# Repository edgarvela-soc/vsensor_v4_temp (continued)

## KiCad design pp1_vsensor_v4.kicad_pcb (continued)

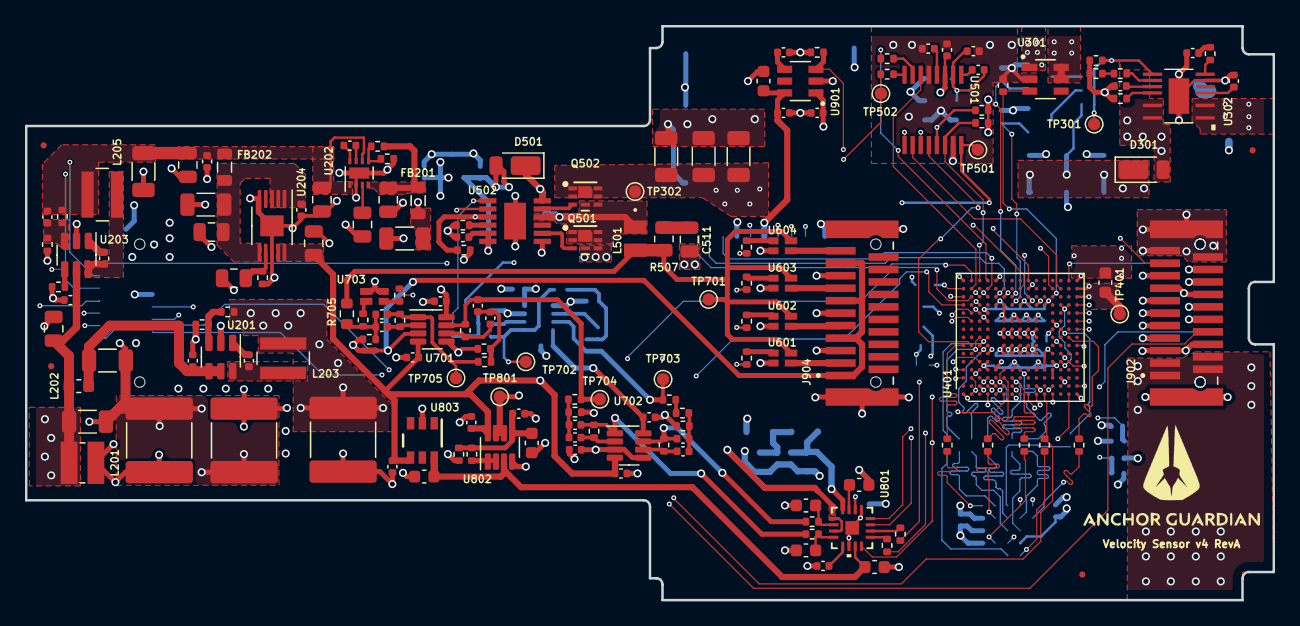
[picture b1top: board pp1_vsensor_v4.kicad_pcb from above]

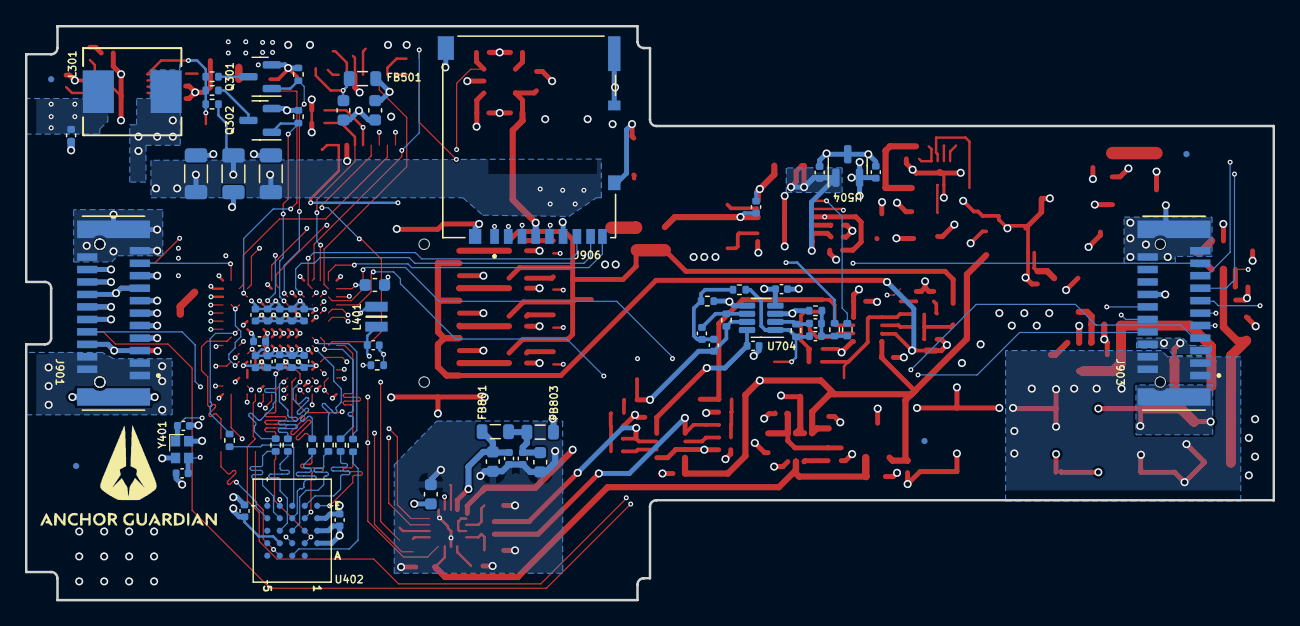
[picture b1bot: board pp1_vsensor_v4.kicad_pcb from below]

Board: 6 copper layers, 100.0 x 46.0 mm, 249 parts (77 on the bottom side), 175 nets.

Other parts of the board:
C302, C508, C509, C510: 1.5u; C_1206_3216Metric
C304, C305, C420: 1u; C_0402_1005Metric
C306: 2.2n; C_0402_1005Metric
Q301, Q302: PMV45EN2; SOT-23
R301: 1M; R_0402_1005Metric
R302: 34k8; R_0402_1005Metric
R303: 71k5; R_0402_1005Metric
R304: 130k; R_0402_1005Metric
R305: 22k1; R_0402_1005Metric
R306: 0R; R_0402_1005Metric
R309, R310, R311, R501, R502: 68k1; R_0402_1005Metric
TP301: VFBDRIVE; TestPoint_Pad_D1.0mm
U302: LT8361; SOP50P490X110-17N

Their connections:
+3V3: C420.1, R501.1, R502.1; also elsewhere on the board
/High Voltage Supply/SWBOOST: U302.14 (SW2), U302.16 (SW1); also elsewhere on the board
/High Voltage Supply/Sync_Mode: R306.1, U302.12 (SYNC/MODE)
/High Voltage Supply/VDriveIN: C305.1, U302.1 (EN/UVLO), U302.3 (VIN); also elsewhere on the board
/High Voltage Supply/VSel0: Q301.1 (G), R310.1; also elsewhere on the board
/High Voltage Supply/VSel1: Q302.1 (G), R309.1; also elsewhere on the board
/Microcontroller/DDS_FSync: R502.2; also elsewhere on the board
/Microcontroller/DDS_Standby: R501.2; also elsewhere on the board
/Microcontroller/HV_ENABLE: R311.1; also elsewhere on the board
unnamed: Q301.3 (D), R302.2
unnamed: Q302.3 (D), R303.2
unnamed: R301.2, R302.1, R303.1, R304.1, TP301.1, U302.9 (FBX)
unnamed: C304.1, U302.5 (INTVCC)
unnamed 132: U302.10 (RT); also elsewhere on the board
unnamed 133: U302.11 (SS); also elsewhere on the board
unnamed: R305.1, U302.8 (VC)

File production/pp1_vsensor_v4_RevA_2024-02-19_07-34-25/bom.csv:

Designator,Footprint,Quantity,Value,LCSC Part #
"C201, C206, C213, C214, C215, C218, C403, C404, C405, C406, C407, C408, C409, C410, C411, C412, C419, C501, C504, C506, C513, C515, C707, C714, C715, C716, C717, C718, C719, C801, C805, C812, C813, C814, C904",0402,35,100n,CC0402KRX7R9BB104
"C202, C203, C207",2220,3,22u,C5750X7R1H226M250KB
"C204, C205",1206,2,4u7,GRM31CR71H475KA12K
"C208, C209, C211, C220, C223, C225, C226",0805,7,4u7,CGA4J3X5R1H475K125AB
"C210, C304, C305, C420, C507, C512, C809, C901, C902",0402,9,1u,UMK105CBJ105MV-F
"C212, C219, C222",1206,3,47u,C3216X5R1C476M160AB
C216,0402,1,39p,CC0402FRNPO9BN390
C217,0805,1,2u2,CGA4J1X7R1V225K125AC
"C301, C302, C303, C508, C509, C510",1206,6,1.5u,C3216X7S2A155K160AB
C306,0402,1,2.2n,C0402C222J5RAC7867
"C307, C502",0402,2,10n,GCM155R71H103KA55D
"C401, C402",0402,2,9p,GRM1555C1H9R0BA01D
C413,0402,1,4u7,04023D475MAT2A
C415,0402,1,220p,0402N221J500CT
"C416, C421, C503, C505, C802, C810, C811, C815, C903",0603,9,10u,GRM188R61E106MA73D
"C701, C704, C708, C711",0402,4,15p,CC0402JRNPO9BN150
"C702, C705, C709, C712",0402,4,20p,CC0402JRNPO9BN200
"C703, C706, C710, C713",0402,4,24p,CC0402JRNPO9BN240
"C803, C804, C806",0603,3,1u,06035C105KAT2A
"C807, C808",0603,2,2n7,CC0603KRX7R9BB272
"D301, D501",D_PowerDI-123,2,DFLS2100-7,DFLS2100-7
"FB201, FB202, FB501, FB801, FB803",0805,5,2.2k/200mA,742792093
"J901, J903",AMPHENOL_10162581-3134121LF,2,10162581-3134121LF,10162581-3134121LF
"J902, J904",AMPHENOL_10162582-1134121LF,2,10162582-1134121LF,10162582-1134121LF
L201,L_Wuerth_MAPI-3020,1,10u,74438336100
L202,0603,1,470nH,LQM18PNR47NC0L
"L203, L205",L_Wuerth_MAPI-4020,2,15u 1.9A,74438356150
L301,IND25X25CZ,1,8u2,IHLP2525CZER8R2M01
L401,Inductor_0806,1,2.2u,DFE201612PD-2R2M=P2
L501,RES_CIGT201610,1,1u/4.2A,CIGT201610EH1R0MNE
"Q301, Q302",SOT-23,2,PMV45EN2,PMV45EN2R
"Q501, Q502",UDFN6B_TOS,2,SSM6K361NU,"SSM6K361NU,LF"
R201,0402,1,69k8,RC0402FR-0769K8L
R202,0402,1,91k,RC0402FR-0791KL
"R203, R209, R305",0402,3,22k1,RC0402FR-0722K1L
"R204, R210, R702, R713",0402,4,40k2,RC0402FR-0740K2L
R207,0402,1,102k,RC0402FR-07102KL
"R208, R309, R310, R311, R501, R502, R505, R703, R712, R720, R912",0402,11,68k1,RC0402FR-0768K1L
R301,0402,1,1M,CRGCQ0402F1M0
R302,0402,1,34k8,RMCF0402FT34K8
"R303, R701",0402,2,71k5,RC0402FR-0771K5L
R304,0402,1,130k,RC0402FR-07130KL
R306,0402,1,0R,RC0402JR-070RL
"R307, R308, R401, R714, R715, R721, R722, R806, R807",0402,9,10k,RC1005F103CS
"R402, R403, R404, R405, R406, R407, R408, R409, R410, R411, R412, R413, R503, R504",0402,14,33R,RC0402JR-0733RL
R506,0402,1,36k5,ERJ-2RKF3652X
"R601, R602, R603, R604, R710",0402,5,270R,RMCF0402FT270R
R704,0402,1,20k5,RC0402FR-0720K5L
R705,0603,1,100k,RC0402FR-07100KL
R706,0402,1,19k6,RC0402FR-0719K6L
"R707, R709, R717, R718",0402,4,2k55,RC0402FR-072K55L
R708,0402,1,1k58,RC0402FR-071K58L
"R711, R719",0402,2,1k47,RC0402FR-071K47L
"R801, R802",0402,2,20R,RC0402FR-0720RL
"R803, R804",0402,2,100R,RC0402FR-07100RL
"U201, U203",SOT-23-6,2,LMR54406,LMR54406FDBVR
U202,WSON-8-1EP_2x2mm_P0.5mm_EP0.9x1.6mm,1,LM27761,LM27761DSGR
U204,MSOP-10-1EP_3x3mm_P0.5mm_EP1.68x1.88mm,1,LT3042EMSE,LT3042EMSE#TRPBF
"U301, U901",SOT95P280X145-6N,2,TPS22810DBV,TPS22810TDBVRQ1
U302,SOP50P490X110-17N,1,LT8361,LT8361HMSE#PBF
U401,UFBGA-201_10x10mm_Layout15x15_P0.65mm,1,STM32H725IGK6,STM32H725IGK6
U402,S27KS0642GABHV020_1,1,S70KL1282,S70KL1282GABHV020
U501,AD5932YRUZ,1,AD5932YRUZ,AD5932YRUZ
U502,LTC7060,1,LTC7060IMSE-PBF,LTC7060IMSE#WTRPBF
U504,SOT-23,1,TLV760_12,TLV76012DBZR
"U601, U602, U603, U604, U703",TLP3409STP_E,5,TLP3409STP_E,"TLP3409S(TP,E"
"U701, U702, U704, U802",SOT-23-8,4,AD8039,AD8039ARTZ-REEL7
U801,AD7383,1,AD7383,AD7383BCPZ-RL7
U803,REF3430,1,REF3430,REF3430TIDBVR
Y401,XTAL_ECS-160-9-37-CKM-TR,1,ECX-1637_25MHz,ECS-250-8-37-RWN-TR

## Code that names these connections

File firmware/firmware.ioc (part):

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Mcu.Name=STM32H725IGKx
Mcu.Package=UFBGA176
Mcu.UserName=STM32H725IGKx
PA0.GPIOParameters=GPIO_Label
PA0.GPIO_Label=TIM_CS
PA0.Signal=S_TIM2_CH1_ETR
PA0_C.GPIOParameters=GPIO_Label
PA0_C.GPIO_Label=AIN_1
PA0_C.Signal=ADCx_INP0
PA11.GPIOParameters=GPIO_Label
PA11.GPIO_Label=DDS_STANDBY
PA11.Signal=GPIO_Output
PA13(JTMS/SWDIO).Mode=Serial_Wire
PA13(JTMS/SWDIO).Signal=DEBUG_JTMS-SWDIO
PA14(JTCK/SWCLK).Mode=Serial_Wire
PA14(JTCK/SWCLK).Signal=DEBUG_JTCK-SWCLK
PA1_C.GPIOParameters=GPIO_Label
PA1_C.GPIO_Label=AIN_2
PA1_C.Signal=ADCx_INP1
PA3.GPIOParameters=GPIO_Label
PA3.GPIO_Label=TIM_SCLK
PA3.Signal=S_TIM15_CH2
PA4.GPIOParameters=GPIO_Label
PA4.GPIO_Label=DDS_FSYNC
PA4.Mode=NSS_Signal_Hard_Output
PA4.Signal=SPI6_NSS
PA6.GPIOParameters=GPIO_Label
PA6.GPIO_Label=DDS_INTERRUPT
PA6.Signal=S_TIM13_CH1
PA7.GPIOParameters=GPIO_Label
PA7.GPIO_Label=DDS_SDA
PA7.Mode=Simplex_Bidirectional_Master
PA7.Signal=SPI6_MOSI
PA8.Mode=Clock-out-1
PA8.Signal=RCC_MCO_1
PA9.GPIOParameters=GPIO_Label
PA9.GPIO_Label=DRV_FAULT
PA9.Signal=GPIO_Input
PB10.GPIOParameters=GPIO_Label
PB10.GPIO_Label=ADC_SCLKA
PB10.Mode=Full_Duplex_Slave
PB10.Signal=SPI2_SCK
PB9.GPIOParameters=GPIO_Label
PB9.GPIO_Label=ADC_CSA
PB9.Mode=NSS_Signal_Hard_Input
PB9.Signal=SPI2_NSS
PC10.GPIOParameters=GPIO_Label
PC10.GPIO_Label=SD_D2
PC10.Mode=SD_4_bits_Wide_bus
PC10.Signal=SDMMC1_D2
PC11.GPIOParameters=GPIO_Label
PC11.GPIO_Label=SD_D3
PC11.Mode=SD_4_bits_Wide_bus
PC11.Signal=SDMMC1_D3
PC12.GPIOParameters=GPIO_Label
PC12.GPIO_Label=SD_CLK
PC12.Mode=SD_4_bits_Wide_bus
PC12.Signal=SDMMC1_CK
PC14-OSC32_IN.GPIOParameters=GPIO_Label
PC14-OSC32_IN.GPIO_Label=Rx_Ena
PC14-OSC32_IN.Signal=GPIO_Output
PC2.GPIOParameters=GPIO_Label
PC2.GPIO_Label=ADC_SDI
PC2.Mode=Full_Duplex_Slave
PC2.Signal=SPI2_MISO
PC3.GPIOParameters=GPIO_Label
PC3.GPIO_Label=ADC_SDOA
PC3.Mode=Full_Duplex_Slave
PC3.Signal=SPI2_MOSI
PC7.GPIOParameters=GPIO_Label
PC7.GPIO_Label=DDS_SYNCOUT
PC7.Signal=GPIO_Input
PC8.GPIOParameters=GPIO_Label
PC8.GPIO_Label=SD_D0
PC8.Mode=SD_4_bits_Wide_bus
PC8.Signal=SDMMC1_D0
PC9.GPIOParameters=GPIO_Label
PC9.GPIO_Label=SD_D1
PC9.Mode=SD_4_bits_Wide_bus
PC9.Signal=SDMMC1_D1
PD12.GPIOParameters=GPIO_Label
PD12.GPIO_Label=VSEN_D1
PD12.Signal=GPIO_Output
PD14.GPIOParameters=GPIO_Label
PD14.GPIO_Label=VSENS_uc_RX
PD14.Mode=Asynchronous
PD14.Signal=UART9_RX
PD15.GPIOParameters=GPIO_Label
PD15.GPIO_Label=VSENS_uc_TX
PD15.Mode=Asynchronous
PD15.Signal=UART9_TX
PD2.GPIOParameters=GPIO_Label
PD2.GPIO_Label=SD_CMD
PD2.Mode=SD_4_bits_Wide_bus
PD2.Signal=SDMMC1_CMD
PE1.GPIOParameters=GPIO_Label
PE1.GPIO_Label=VSENS_D2
PE1.Signal=GPIO_Output
PE12.GPIOParameters=GPIO_Label
PE12.GPIO_Label=ADC_SCLKB
PE12.Mode=Simplex_Bidirectional_Slave
PE12.Signal=SPI4_SCK
PE4.GPIOParameters=GPIO_Label
PE4.GPIO_Label=ADC_CSB
PE4.Mode=NSS_Signal_Hard_Input
PE4.Signal=SPI4_NSS
PE5.GPIOParameters=GPIO_Label
PE5.GPIO_Label=ADC_SDOB
PE5.Mode=Simplex_Bidirectional_Slave
PE5.Signal=SPI4_MISO
PF0.GPIOParameters=GPIO_Label
PF0.GPIO_Label=uc_dram_dq0
PF0.Mode=OCTOSPI2_IOL_Port2L
PF0.Signal=OCTOSPIM_P2_IO0
PF1.GPIOParameters=GPIO_Label
PF1.GPIO_Label=uc_dram_dq1
PF1.Mode=OCTOSPI2_IOL_Port2L
PF1.Signal=OCTOSPIM_P2_IO1
PF11.GPIOParameters=GPIO_Label
PF11.GPIO_Label=DRV_EN
PF11.Mode=PWM Generation1 CH1
PF11.Signal=TIM24_CH1
PF2.GPIOParameters=GPIO_Label
PF2.GPIO_Label=uc_dram_dq2
PF2.Mode=OCTOSPI2_IOL_Port2L
PF2.Signal=OCTOSPIM_P2_IO2
PF3.GPIOParameters=GPIO_Label
PF3.GPIO_Label=uc_dram_dq3
PF3.Mode=OCTOSPI2_IOL_Port2L
PF3.Signal=OCTOSPIM_P2_IO3
PF4.GPIOParameters=GPIO_Label
PF4.GPIO_Label=uc_dram_ck
PF4.Mode=O2_P2_CLK
PF4.Signal=OCTOSPIM_P2_CLK
PG0.GPIOParameters=GPIO_Label
PG0.GPIO_Label=uc_dram_dq4
PG0.Mode=OCTOSPI2_IOH_Port2H
PG0.Signal=OCTOSPIM_P2_IO4
PG1.GPIOParameters=GPIO_Label
PG1.GPIO_Label=uc_dram_dq5
PG1.Mode=OCTOSPI2_IOH_Port2H
PG1.Signal=OCTOSPIM_P2_IO5
PG10.GPIOParameters=GPIO_Label
PG10.GPIO_Label=uc_dram_dq6
PG10.Mode=OCTOSPI2_IOH_Port2H
PG10.Signal=OCTOSPIM_P2_IO6
PG11.GPIOParameters=GPIO_Label
PG11.GPIO_Label=uc_dram_dq7
PG11.Mode=OCTOSPI2_IOH_Port2H
PG11.Signal=OCTOSPIM_P2_IO7
PG12.GPIOParameters=GPIO_Label
PG12.GPIO_Label=uc_dram_ncs
PG12.Mode=OCTOSPI2_Port2_NCS
PG12.Signal=OCTOSPIM_P2_NCS
PG13.GPIOParameters=GPIO_Label
PG13.GPIO_Label=DDS_SCLK
PG13.Mode=Simplex_Bidirectional_Master
PG13.Signal=SPI6_SCK
PG15.GPIOParameters=GPIO_Label
PG15.GPIO_Label=uc_dram_rwds
PG15.Mode=OCTOSPI2_Port2_DQS
PG15.Signal=OCTOSPIM_P2_DQS
PH10.GPIOParameters=GPIO_Label
PH10.GPIO_Label=DDS_CTRL
PH10.Signal=S_TIM5_CH1
PH14.GPIOParameters=GPIO_Label
PH14.GPIO_Label=SD_EN3V3
PH14.Signal=GPIO_Output
PH15.GPIOParameters=GPIO_Label
PH15.GPIO_Label=SD_DETECT
PH15.Signal=GPIO_Output
PH9.GPIOParameters=GPIO_Label
PH9.GPIO_Label=VSENS_D0
PH9.Signal=S_TIM12_CH2
RCC.SYSCLKFreq_VALUE=64000000
board=custom

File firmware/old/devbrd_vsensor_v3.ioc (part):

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Mcu.Name=STM32H735IGKx
Mcu.Package=UFBGA176
Mcu.UserName=STM32H735IGKx
PA0.Signal=S_TIM2_CH1_ETR
PA3.Signal=S_TIM15_CH2
PA5.GPIOParameters=GPIO_Label
PA5.GPIO_Label=DDS_SCLK
PA5.Mode=Simplex_Bidirectional_Master
PA5.Signal=SPI6_SCK
PA8.GPIOParameters=GPIO_Label
PA8.GPIO_Label=DDS_MCLK 
PA8.Mode=Clock-out-1
PA8.Signal=RCC_MCO_1
PB14.GPIOParameters=GPIO_Speed,GPIO_Label
PB14.GPIO_Label=ADC_SDI
PB14.GPIO_Speed=GPIO_SPEED_FREQ_VERY_HIGH
PB14.Mode=Full_Duplex_Slave
PB14.Signal=SPI2_MISO
PB15.GPIOParameters=GPIO_Speed,GPIO_Label
PB15.GPIO_Label=ADC_SDOA
PB15.GPIO_Speed=GPIO_SPEED_FREQ_VERY_HIGH
PB15.Mode=Full_Duplex_Slave
PB15.Signal=SPI2_MOSI
PB9.GPIOParameters=GPIO_Speed,GPIO_Label
PB9.GPIO_Label=ADC_CS
PB9.GPIO_Speed=GPIO_SPEED_FREQ_VERY_HIGH
PB9.Mode=NSS_Signal_Hard_Input
PB9.Signal=SPI2_NSS
PC10.GPIOParameters=GPIO_PuPd
PC10.GPIO_PuPd=GPIO_PULLUP
PC10.Mode=SD_4_bits_Wide_bus
PC10.Signal=SDMMC1_D2
PC11.GPIOParameters=GPIO_PuPd
PC11.GPIO_PuPd=GPIO_PULLUP
PC11.Mode=SD_4_bits_Wide_bus
PC11.Signal=SDMMC1_D3
PC12.Mode=SD_4_bits_Wide_bus
PC12.Signal=SDMMC1_CK
PC13.GPIOParameters=GPIO_Label
PC13.GPIO_Label=USR_BTN
PC13.Signal=GPIO_Input
PC2.GPIOParameters=GPIO_Label
PC2.GPIO_Label=LED_GREEN
PC2.Signal=GPIO_Output
PC3.GPIOParameters=GPIO_Label
PC3.GPIO_Label=LED_RED
PC3.Signal=GPIO_Output
PC8.GPIOParameters=GPIO_PuPd
PC8.GPIO_PuPd=GPIO_PULLUP
PC8.Mode=SD_4_bits_Wide_bus
PC8.Signal=SDMMC1_D0
PC9.GPIOParameters=GPIO_PuPd
PC9.GPIO_PuPd=GPIO_PULLUP
PC9.Mode=SD_4_bits_Wide_bus
PC9.Signal=SDMMC1_D1
PD14.GPIOParameters=GPIO_Label
PD14.GPIO_Label=VSEL1
PD14.Signal=GPIO_Output
PD15.GPIOParameters=GPIO_Label
PD15.GPIO_Label=EN_5V0
PD15.Signal=GPIO_Output
PD2.GPIOParameters=GPIO_PuPd
PD2.GPIO_PuPd=GPIO_PULLUP
PD2.Mode=SD_4_bits_Wide_bus
PD2.Signal=SDMMC1_CMD
PD3.GPIOParameters=GPIO_Speed,GPIO_Label
PD3.GPIO_Label=ADC_SCLK
PD3.GPIO_Speed=GPIO_SPEED_FREQ_VERY_HIGH
PD3.Mode=Full_Duplex_Slave
PD3.Signal=SPI2_SCK
PE10.GPIOParameters=GPIO_Label
PE10.GPIO_Label=XDCR_SEL2
PE10.Signal=GPIO_Output
PE11.GPIOParameters=GPIO_Speed,GPIO_Label
PE11.GPIO_Label=ADC_CS2
PE11.GPIO_Speed=GPIO_SPEED_FREQ_VERY_HIGH
PE11.Mode=NSS_Signal_Hard_Input
PE11.Signal=SPI4_NSS
PE12.GPIOParameters=GPIO_Speed,GPIO_Label
PE12.GPIO_Label=ADC_SCLK2
PE12.GPIO_Speed=GPIO_SPEED_FREQ_VERY_HIGH
PE12.Mode=Simplex_Bidirectional_Slave
PE12.Signal=SPI4_SCK
PE13.GPIOParameters=GPIO_Speed,GPIO_Label
PE13.GPIO_Label=ADC_SDOB
PE13.GPIO_Speed=GPIO_SPEED_FREQ_VERY_HIGH
PE13.Mode=Simplex_Bidirectional_Slave
PE13.Signal=SPI4_MISO
PE14.GPIOParameters=GPIO_Label
PE14.GPIO_Label=DRV_FAULT
PE14.Signal=GPIO_Input
PE7.GPIOParameters=GPIO_Label
PE7.GPIO_Label=VSEL2
PE7.Signal=GPIO_Output
PE9.GPIOParameters=GPIO_Label
PE9.GPIO_Label=XDCR_SEL1
PE9.Signal=GPIO_Output
PF0.Mode=OCTOSPI2_IOL_Port2L
PF0.Signal=OCTOSPIM_P2_IO0
PF1.Mode=OCTOSPI2_IOL_Port2L
PF1.Signal=OCTOSPIM_P2_IO1
PF11.Signal=TIM24_CH1
PF12.Mode=OCTOSPI2_Port2_DQS
PF12.Signal=OCTOSPIM_P2_DQS
PF13.GPIOParameters=GPIO_Label
PF13.GPIO_Label=XDCR_SEL3
PF13.Signal=GPIO_Output
PF14.GPIOParameters=GPIO_PuPd,GPIO_Label
PF14.GPIO_Label=DDS_STANDBY
PF14.GPIO_PuPd=GPIO_PULLDOWN
PF14.Signal=GPIO_Output
PF15.GPIOParameters=GPIO_Label
PF15.GPIO_Label=SD_EN3V3
PF15.Signal=GPIO_Output
PF2.Mode=OCTOSPI2_IOL_Port2L
PF2.Signal=OCTOSPIM_P2_IO2
PF3.Mode=OCTOSPI2_IOL_Port2L
PF3.Signal=OCTOSPIM_P2_IO3
PF4.Mode=O2_P2_CLK
PF4.Signal=OCTOSPIM_P2_CLK
PF5.GPIOParameters=GPIO_Label
PF5.GPIO_Label=SD_DETECT
PF5.Signal=GPIO_Input
PF6.GPIOParameters=GPIO_Speed,PinState,GPIO_Label
PF6.GPIO_Label=DDS_FSYNC
PF6.GPIO_Speed=GPIO_SPEED_FREQ_MEDIUM
PF6.PinState=GPIO_PIN_SET
PF6.Signal=GPIO_Output
PF7.GPIOParameters=GPIO_Label
PF7.GPIO_Label=LED_BLUE
PF7.Signal=GPIO_Output
PF8.GPIOParameters=GPIO_Label
PF8.GPIO_Label=DDS_INTERRUPT
PF8.Signal=GPIO_Output
PF9.GPIOParameters=GPIO_Label
PF9.GPIO_Label=DDS_CTRL
PF9.Signal=GPIO_Output
PG0.Mode=OCTOSPI2_IOH_Port2H
PG0.Signal=OCTOSPIM_P2_IO4
PG1.Mode=OCTOSPI2_IOH_Port2H
PG1.Signal=OCTOSPIM_P2_IO5
PG10.Mode=OCTOSPI2_IOH_Port2H
PG10.Signal=OCTOSPIM_P2_IO6
PG11.Mode=OCTOSPI2_IOH_Port2H
PG11.Signal=OCTOSPIM_P2_IO7
PG12.Mode=OCTOSPI2_Port2_NCS
PG12.Signal=OCTOSPIM_P2_NCS
PG14.GPIOParameters=GPIO_Label
PG14.GPIO_Label=DDS_SDA
PG14.Mode=Simplex_Bidirectional_Master
PG14.Signal=SPI6_MOSI
PG3.GPIOParameters=GPIO_Label
PG3.GPIO_Label=AFE_GAIN
PG3.Signal=GPIO_Output
PG4.GPIOParameters=GPIO_Label
PG4.GPIO_Label=DRIVE_EN
PG4.Signal=GPIO_Output
PG5.GPIOParameters=GPIO_Label
PG5.GPIO_Label=HV_ENABLE
PG5.Signal=GPIO_Output
PH1-OSC_OUT.GPIOParameters=GPIO_Label
PH1-OSC_OUT.GPIO_Label=VSEL0
PH1-OSC_OUT.Signal=GPIO_Output
PH10.Signal=S_TIM5_CH1
PH12.GPIOParameters=GPIO_Label
PH12.GPIO_Label=XDCR_SEL4
PH12.Signal=GPIO_Output
PH7.GPIOParameters=GPIO_Label
PH7.GPIO_Label=DDS_SYNCOUT
PH7.Signal=GPXTI7
RCC.SYSCLKFreq_VALUE=192000000
RCC.SYSCLKSource=RCC_SYSCLKSOURCE_PLLCLK
board=custom

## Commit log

2024-06-10 added
